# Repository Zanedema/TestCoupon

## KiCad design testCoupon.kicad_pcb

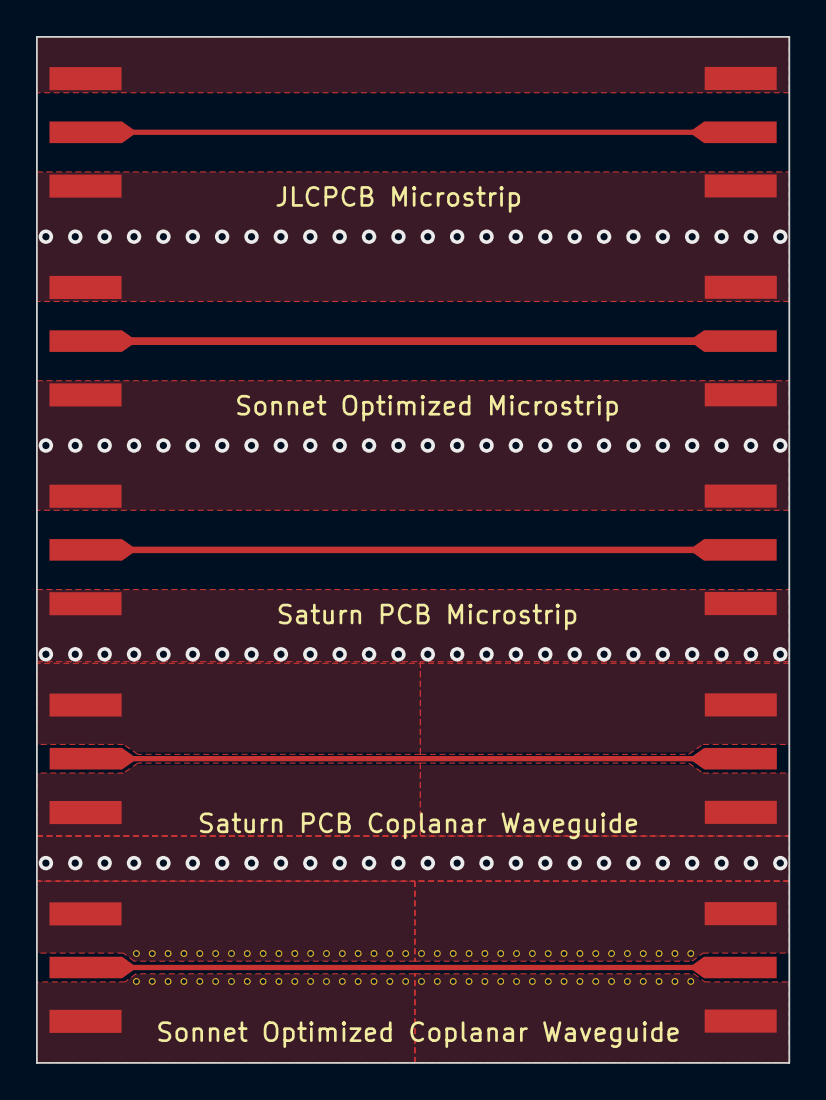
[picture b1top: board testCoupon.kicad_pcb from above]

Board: 4 copper layers, 41.8 x 57.0 mm, 12 parts (0 on the bottom side), 6 nets.

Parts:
J1, J2, J3, J4, J5, J6, J7, J8, J9, J10: Conn_Coaxial; ebaySMA
NT4: Saturn CPWG; SaturnCPWG
NT5: Sonnet CPWG; SonnetCPWG

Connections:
GND: J1.2 (Ext), J2.2 (Ext), J3.2 (Ext), J4.2 (Ext), J5.2 (Ext), J6.2 (Ext), J7.2 (Ext), J8.2 (Ext), J9.2 (Ext), J10.2 (Ext), NT5.2
unnamed: J1.1 (In), J2.1 (In)
unnamed: J3.1 (In), J4.1 (In)
unnamed: J5.1 (In), J6.1 (In)
unnamed: J7.1 (In), NT4.1
unnamed: J9.1 (In), NT5.1

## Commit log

2022-07-22 a
    the internet is forever and so is this commit
2022-07-22 fab files
2022-07-22 why me
    whyyyyyy
    whyyyyyyyyyyyyyyyyy
    whyyyyyyyyyyyyyyyyyyyyyyyyyyy
2022-08-13 data got
    ah that took a bit.
2022-08-13 yep
    yep

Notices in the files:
testCoupon.kicad_pcb:
Made with <3 in San Diego - MIT Licence
